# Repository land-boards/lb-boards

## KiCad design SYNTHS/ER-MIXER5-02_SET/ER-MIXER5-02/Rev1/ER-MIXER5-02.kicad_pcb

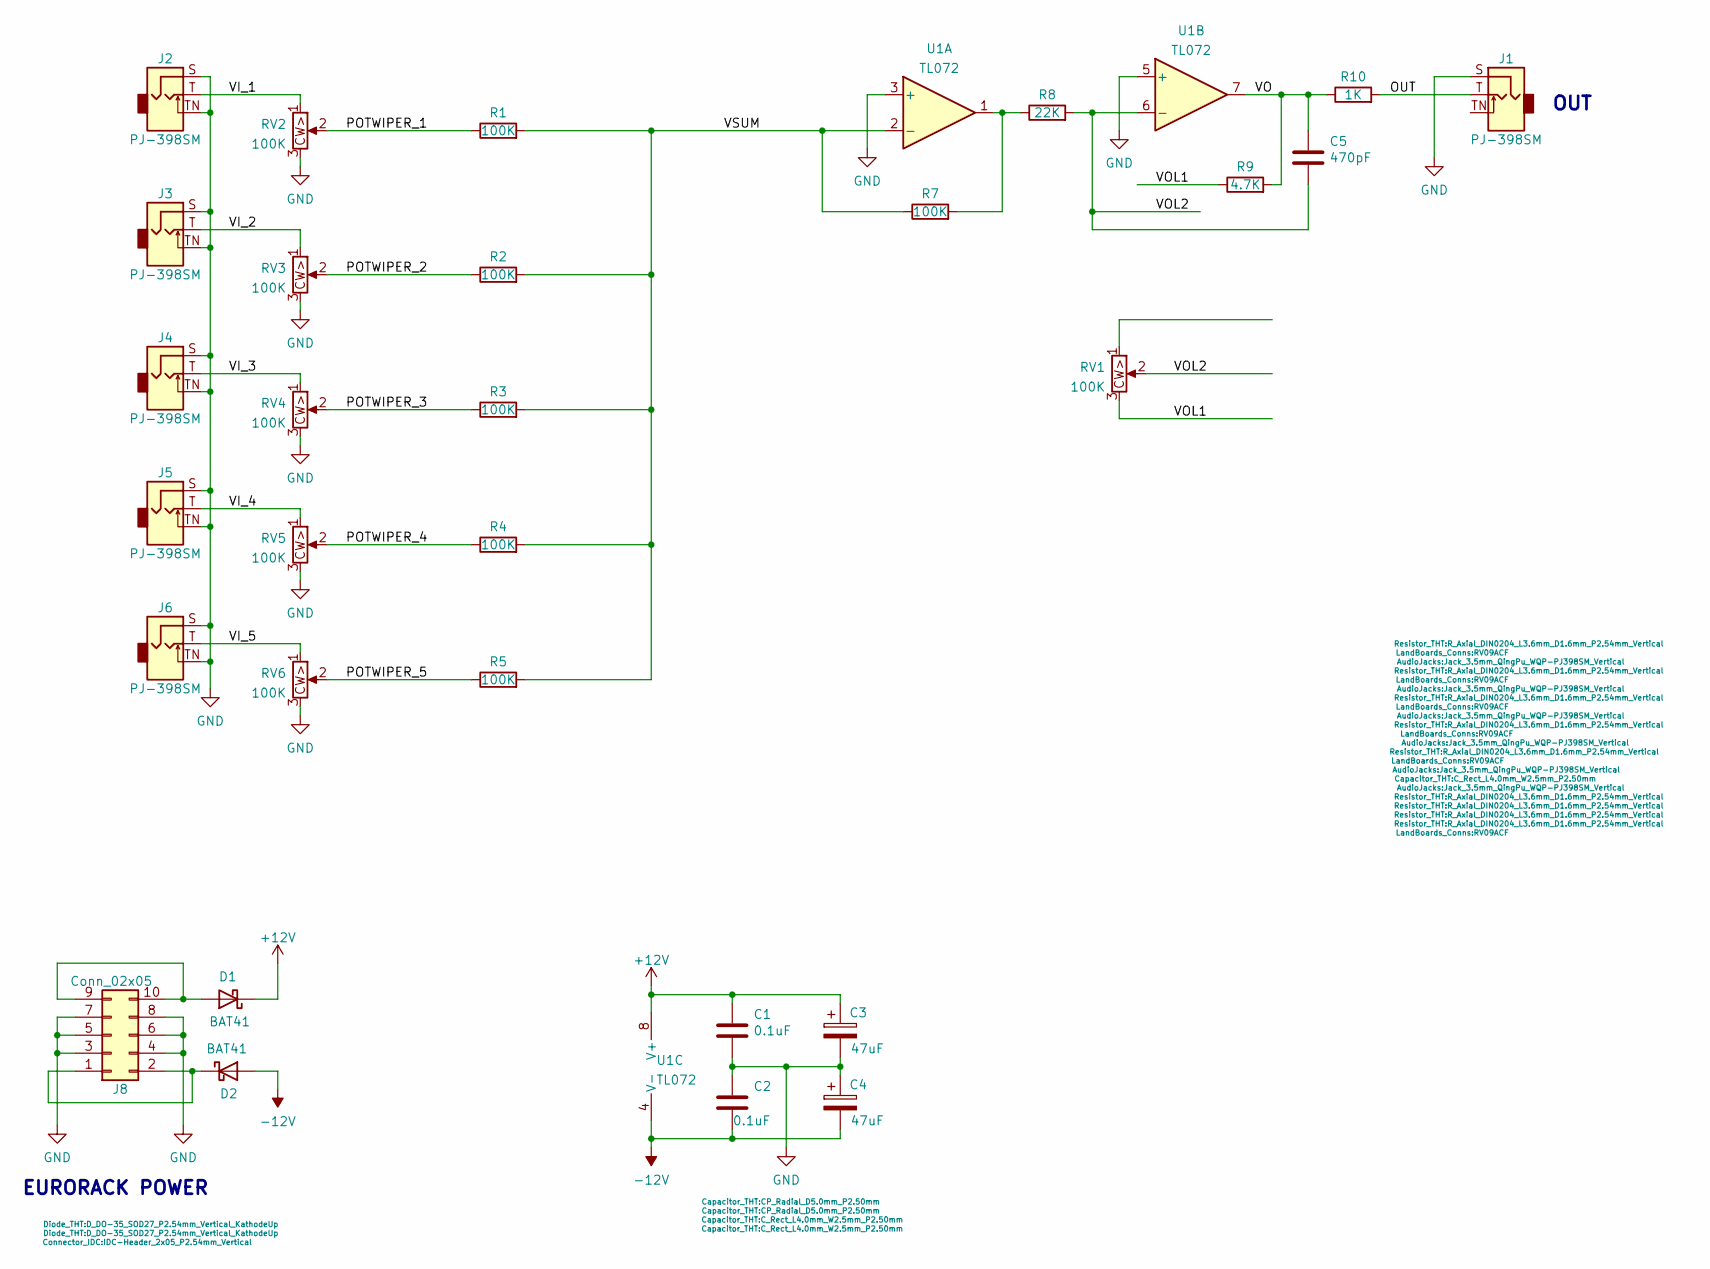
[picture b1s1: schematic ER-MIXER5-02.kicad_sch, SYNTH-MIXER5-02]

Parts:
C1, C2: 0.1uF; C_Rect_L4.0mm_W2.5mm_P2.50mm
C3, C4: 47uF; CP_Radial_D5.0mm_P2.50mm
C5: 470pF; C_Rect_L4.0mm_W2.5mm_P2.50mm
D1, D2: BAT41; D_DO-35_SOD27_P2.54mm_Vertical_KathodeUp
J1, J2, J3, J4, J5, J6: PJ-398SM; Jack_3.5mm_QingPu_WQP-PJ398SM_Vertical
J8: Conn_02x05; IDC-Header_2x05_P2.54mm_Vertical
R1, R2, R3, R4, R5, R7: 100K; R_Axial_DIN0204_L3.6mm_D1.6mm_P2.54mm_Vertical
R8: 22K; R_Axial_DIN0204_L3.6mm_D1.6mm_P2.54mm_Vertical
R9: 4.7K; R_Axial_DIN0204_L3.6mm_D1.6mm_P2.54mm_Vertical
R10: 1K; R_Axial_DIN0204_L3.6mm_D1.6mm_P2.54mm_Vertical
RV1, RV2, RV3, RV4, RV5, RV6: 100K; RV09ACF
U1: TL072; DIP-8_W7.62mm

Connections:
+12V: C1.1, C3.1, D1.1 (K), U1.8 (V+)
-12V: C2.2, C4.2, D2.2 (A), U1.4 (V-)
/OUT: J1.T, R10.2
/POTWIPER_1: R1.1, RV2.2
/POTWIPER_2: R2.1, RV3.2
/POTWIPER_3: R3.1, RV4.2
/POTWIPER_4: R4.1, RV5.2
/POTWIPER_5: R5.1, RV6.2
/VI_1: J2.T, RV2.1
/VI_2: J3.T, RV3.1
/VI_3: J4.T, RV4.1
/VI_4: J5.T, RV5.1
/VI_5: J6.T, RV6.1
/VO: C5.1, R9.2, R10.1, U1.7
/VOL1: R9.1, RV1.3
/VOL2: C5.2, R8.2, RV1.2, U1.6 (-)
/VSUM: R1.2, R2.2, R3.2, R4.2, R5.2, R7.1, U1.2 (-)
GND: C1.2, C2.1, C3.2, C4.1, J1.S, J2.S, J2.TN, J3.S, J3.TN, J4.S, J4.TN, J5.S, J5.TN, J6.S, J6.TN, J8.3, J8.4, J8.5, J8.6, J8.7, J8.8, RV2.3, RV3.3, RV4.3, RV5.3, RV6.3, U1.3 (+), U1.5 (+)
unnamed: D1.2 (A), J8.9, J8.10
unnamed: D2.1 (K), J8.1, J8.2
unnamed: R7.2, R8.1, U1.1

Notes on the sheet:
EURORACK POWER
OUT

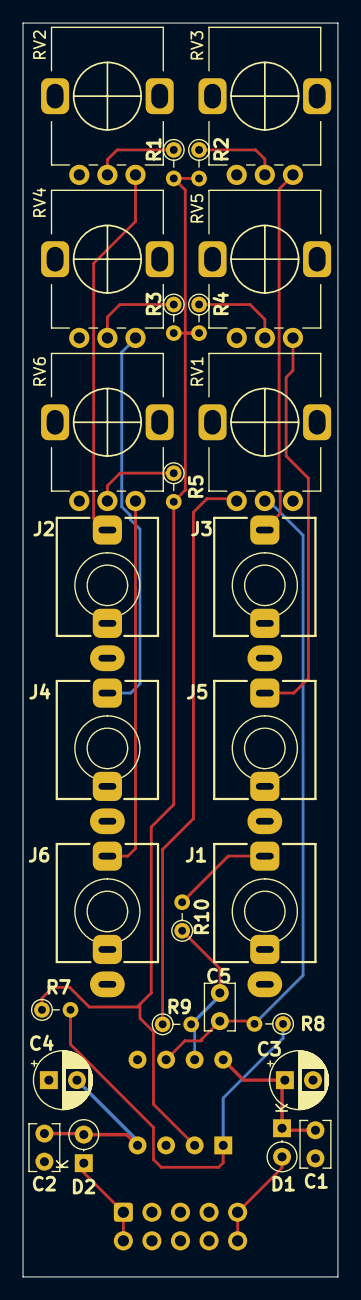
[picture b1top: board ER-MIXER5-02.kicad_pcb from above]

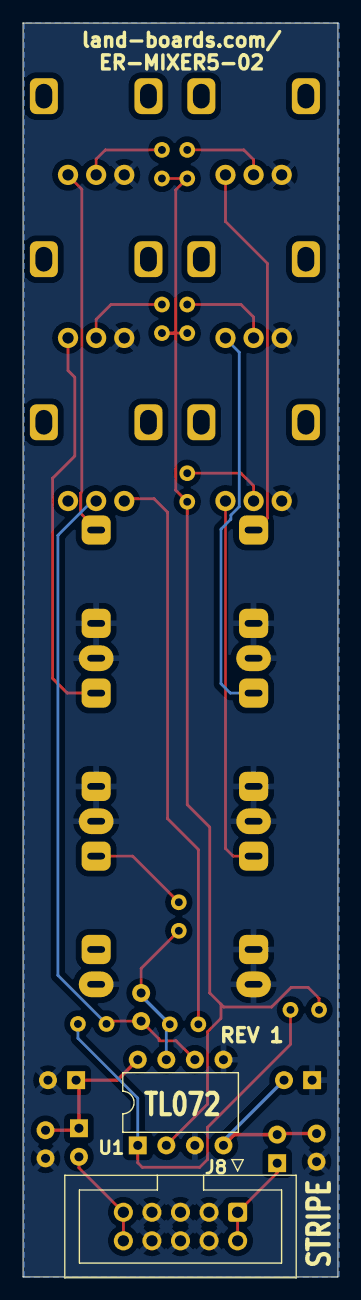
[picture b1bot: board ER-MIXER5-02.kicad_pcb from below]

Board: 2 copper layers, 28.0 x 111.5 mm, 30 parts (2 on the bottom side), 21 nets.

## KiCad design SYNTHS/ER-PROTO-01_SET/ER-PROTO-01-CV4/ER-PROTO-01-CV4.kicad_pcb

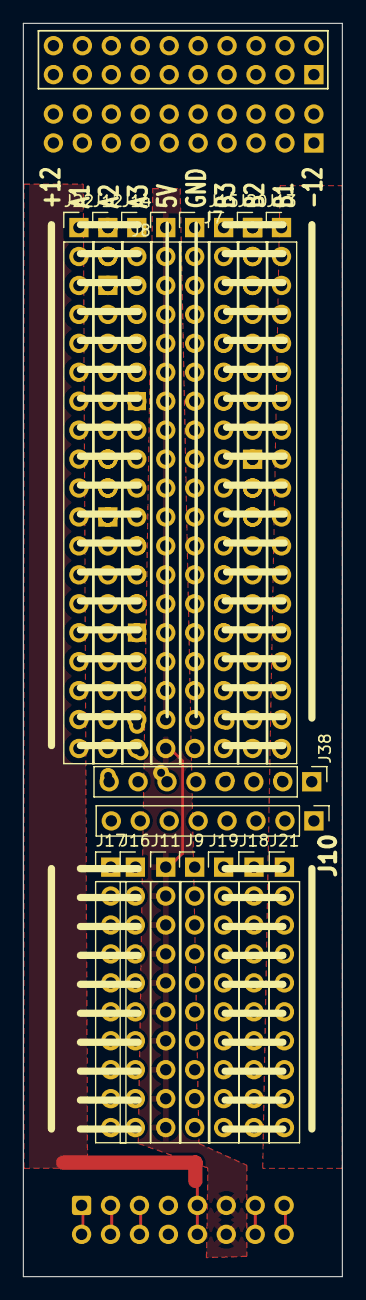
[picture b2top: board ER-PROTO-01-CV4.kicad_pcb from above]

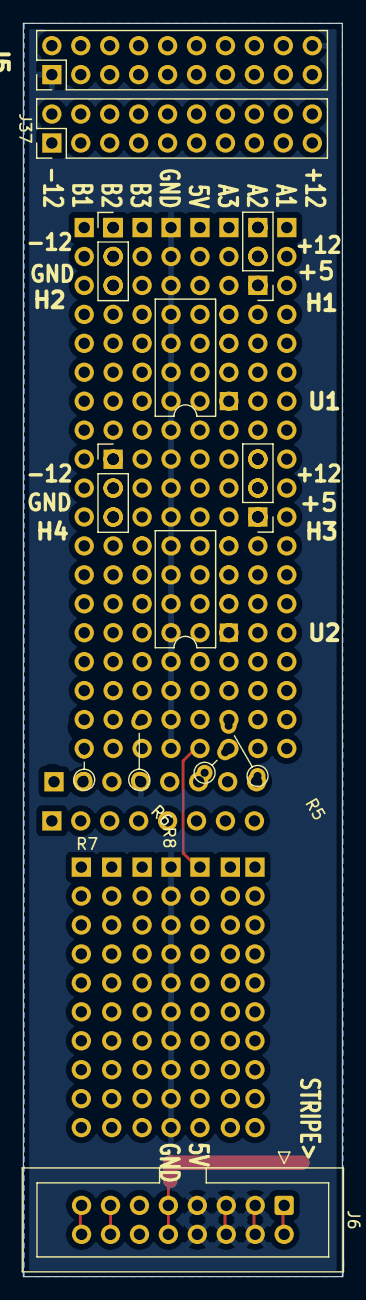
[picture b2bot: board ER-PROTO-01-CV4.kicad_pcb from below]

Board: 2 copper layers, 28.0 x 110.0 mm, 30 parts (13 on the bottom side), 27 nets.

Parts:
H1, H2, H3, H4: Conn_01x03; PinHeader_1x03_P2.54mm_Vertical
J5: HEADER, 2X10; PinHeader_2x10_P2.54mm_Vertical
J6: HEADER, 2X8; IDC-Header_2x08_P2.54mm_Vertical
J7, J8, J12, J13, J14, J15, J20, J22: Conn_01x19; PinHeader_1x19_P2.54mm_Vertical
J9, J11, J16, J17, J18, J19, J21: Conn_01x10; PinHeader_1x10_P2.54mm_Vertical
J10: Conn_01x08; PinHeader_1x08_P2.54mm_Vertical
J37: PROTO01_POTS; PinHeader_2x10_P2.54mm_Vertical
J38: PROTO01_JACKS; PinHeader_1x08_P2.54mm_Vertical
R5, R8: 1K; R_Axial_DIN0204_L3.6mm_D1.6mm_P5.08mm_Vertical
R6, R7: 1K; R_Axial_DIN0204_L3.6mm_D1.6mm_P2.54mm_Vertical
U1, U2: TL072; DIP-8_W7.62mm

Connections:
+5V: H1.1, H3.1, J6.11, J6.12, J8.1, J8.2, J8.3, J8.4, J8.5, J8.6, J8.7, J8.8, J8.9, J8.10, J8.11, J8.12, J8.13, J8.14, J8.15, J8.16, J8.17, J8.18, J8.19, J11.1, J11.2, J11.3, J11.4, J11.5, J11.6, J11.7, J11.8, J11.9, J11.10
+12V: H1.3, H3.3, J6.9, J6.10
-12V: H2.1, H4.1, J6.1, J6.2
/CV: J6.13, J6.14
/GATE: J6.15, J6.16
/J1-T: J38.8 (J1_T), R5.1
/J2-T: J38.4 (J2_T), R8.1
/J3-T: J38.6 (J3_T), R6.1
/J4-S_X: J10.1, J10.3, J10.5, J10.7
/J4-T: J38.2 (J4_T), R7.1
/POT1-1: J5.8, J5.17
/POT1-3: J5.10, J5.19
/POT1W: J37.18 (POT1_2_W), U1.3 (+)
/POT2W: J37.9 (POT2_2_W), U1.5 (+)
/POT3-1: J5.5, J5.14
/POT3-3: J5.7, J5.16
/POT3W: J37.15 (POT3_2_W), U2.3 (+)
/POT4W: J37.6 (POT4_2_W), U2.5 (+)
/VH1: H1.2, J37.8 (POT2_1_CW), U1.8 (V+)
/VH2: H3.2, J37.5 (POT4_1_CW), U2.8 (V+)
/VL1: H2.2, J37.10 (POT2_3_CCW), U1.4 (V-)
/VL2: H4.2, J37.7 (POT4_3_CCW), U2.4 (V-)
GND: H2.3, H4.3, J5.1, J5.20, J6.3, J6.4, J6.5, J6.6, J6.7, J6.8, J7.1, J7.2, J7.3, J7.4, J7.5, J7.6, J7.7, J7.8, J7.9, J7.10, J7.11, J7.12, J7.13, J7.14, J7.15, J7.16, J7.17, J7.18, J7.19, J9.1, J9.2, J9.3, J9.4, J9.5, J9.6, J9.7, J9.8, J9.9, J9.10, J38.5 (J3_S)
unnamed: R5.2, U1.1, U1.2 (-)
unnamed: R8.2, U1.6 (-), U1.7
unnamed: R6.2, U2.1, U2.2 (-)
unnamed: R7.2, U2.6 (-), U2.7

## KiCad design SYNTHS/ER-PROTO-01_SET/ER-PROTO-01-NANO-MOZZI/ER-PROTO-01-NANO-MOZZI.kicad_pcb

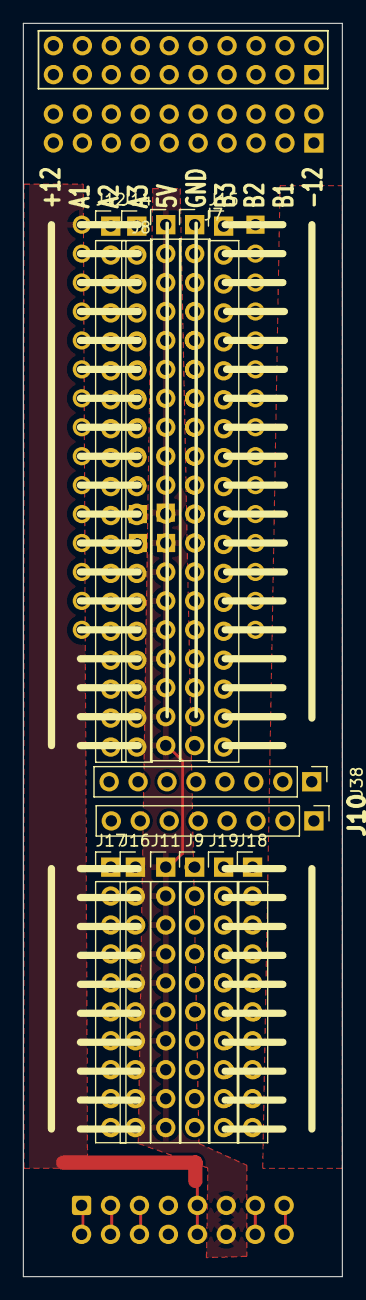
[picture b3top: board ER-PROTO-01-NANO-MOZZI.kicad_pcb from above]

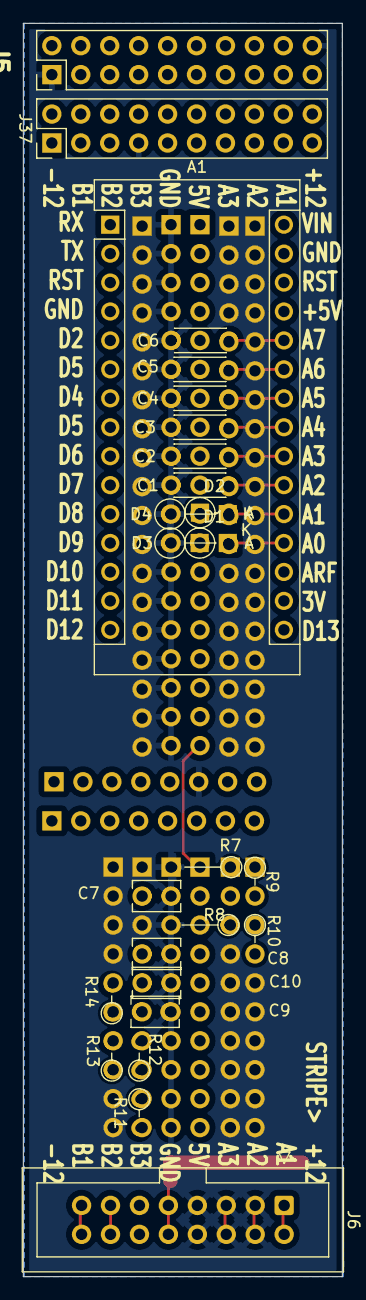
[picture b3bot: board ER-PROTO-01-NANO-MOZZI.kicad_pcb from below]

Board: 2 copper layers, 28.0 x 110.0 mm, 39 parts (26 on the bottom side), 29 nets.

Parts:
A1: Arduino_Nano_v3.x; Arduino_Nano
C1, C2, C3, C4, C5, C6: 0.1uF; C_Disc_D4.3mm_W1.9mm_P5.00mm
C7, C8: 0.1uF; C_Rect_L4.0mm_W2.5mm_P2.50mm
C9: 4.7nF; C_Rect_L4.0mm_W2.5mm_P2.50mm
C10: 10nF; C_Rect_L4.0mm_W2.5mm_P2.50mm
D1, D2: BAT41; D_DO-35_SOD27_P2.54mm_Vertical_AnodeUp
D3, D4: BAT41; D_DO-35_SOD27_P5.08mm_Vertical_KathodeUp
J5: HEADER, 2X10; PinHeader_2x10_P2.54mm_Vertical
J6: HEADER, 2X8; IDC-Header_2x08_P2.54mm_Vertical
J7, J8, J12, J14, J15: Conn_01x19; PinHeader_1x19_P2.54mm_Vertical
J9, J11, J16, J17, J18, J19: Conn_01x10; PinHeader_1x10_P2.54mm_Vertical
J10: Conn_01x08; PinHeader_1x08_P2.54mm_Vertical
J37: PROTO01_POTS; PinHeader_2x10_P2.54mm_Vertical
J38: PROTO01_JACKS; PinHeader_1x08_P2.54mm_Vertical
R7, R8: 100K; R_Axial_DIN0204_L3.6mm_D1.6mm_P5.08mm_Vertical
R9, R10: 10K; R_Axial_DIN0204_L3.6mm_D1.6mm_P2.54mm_Vertical
R11, R14: 3.9K; R_Axial_DIN0204_L3.6mm_D1.6mm_P2.54mm_Vertical
R12, R13: 1M; R_Axial_DIN0204_L3.6mm_D1.6mm_P2.54mm_Vertical

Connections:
+5V: D1.1 (K), D2.1 (K), J6.11, J6.12, J8.1, J8.2, J8.3, J8.4, J8.5, J8.6, J8.7, J8.8, J8.9, J8.10, J8.11, J8.12, J8.13, J8.14, J8.15, J8.16, J8.17, J8.18, J8.19, J11.1, J11.2, J11.3, J11.4, J11.5, J11.6, J11.7, J11.8, J11.9, J11.10
+5VD: A1.27 (+5V), J37.11 (POT5_1_CW)
+12V: A1.30 (VIN), J6.9, J6.10
-12V: J6.1, J6.2
/ANA0: A1.19 (A0), C7.1, D1.2 (A), D3.1 (K), R9.2
/ANA1: A1.20 (A1), C8.1, D2.2 (A), D4.1 (K), R10.2
/ANA2: A1.21 (A2), C1.1, J37.3 (POT6_2_W)
/ANA3: A1.22 (A3), C2.1, J37.6 (POT4_2_W)
/ANA4: A1.23 (A4), C3.1, J37.9 (POT2_2_W)
/ANA5: A1.24 (A5), C4.1, J37.12 (POT5_2_W)
/ANA6: A1.25 (A6), C5.1, J37.15 (POT3_2_W)
/ANA7: A1.26 (A7), C6.1, J37.18 (POT1_2_W)
/CV: J6.13, J6.14
/D9: A1.12 (D9), R11.1
/D10: A1.13 (D10), R12.1, R13.1
/GATE: J6.15, J6.16
/J1-T: J10.8, J38.1 (J1_T), R7.1, R9.1
/J2-S: J10.1, J10.3, J10.5, J10.7
/J2-T: J10.4, J38.5 (J2_T), R8.1, R10.1
/J3-T: J10.6, J38.3 (J3_T)
/J4-T: C10.1, J10.2, J38.7 (J4_T), R14.2
/POT2-1: J5.2, J5.5, J5.8
/POT2-3: J5.4, J5.7, J5.10
/POT5-1: J5.11, J5.14, J5.17
/POT5-3: J5.13, J5.16, J5.19
GND: C1.2, C2.2, C3.2, C4.2, C5.2, C6.2, C7.2, C8.2, C9.2, C10.2, D3.2 (A), D4.2 (A), J5.1, J5.20, J6.3, J6.4, J6.5, J6.6, J6.7, J6.8, J7.1, J7.2, J7.3, J7.4, J7.5, J7.6, J7.7, J7.8, J7.9, J7.10, J7.11, J7.12, J7.13, J7.14, J7.15, J7.16, J7.17, J7.18, J7.19, J9.1, J9.2, J9.3, J9.4, J9.5, J9.6, J9.7, J9.8, J9.9, J9.10, J37.7 (POT4_3_CCW), J38.6 (J2_S), R7.2, R8.2
unnamed: C9.1, R11.2, R12.2, R13.2, R14.1
unnamed: J37.4 (POT6_3_CCW), J37.16 (POT3_3_CCW)
unnamed: J37.8 (POT2_1_CW), J37.14 (POT3_1_CW)

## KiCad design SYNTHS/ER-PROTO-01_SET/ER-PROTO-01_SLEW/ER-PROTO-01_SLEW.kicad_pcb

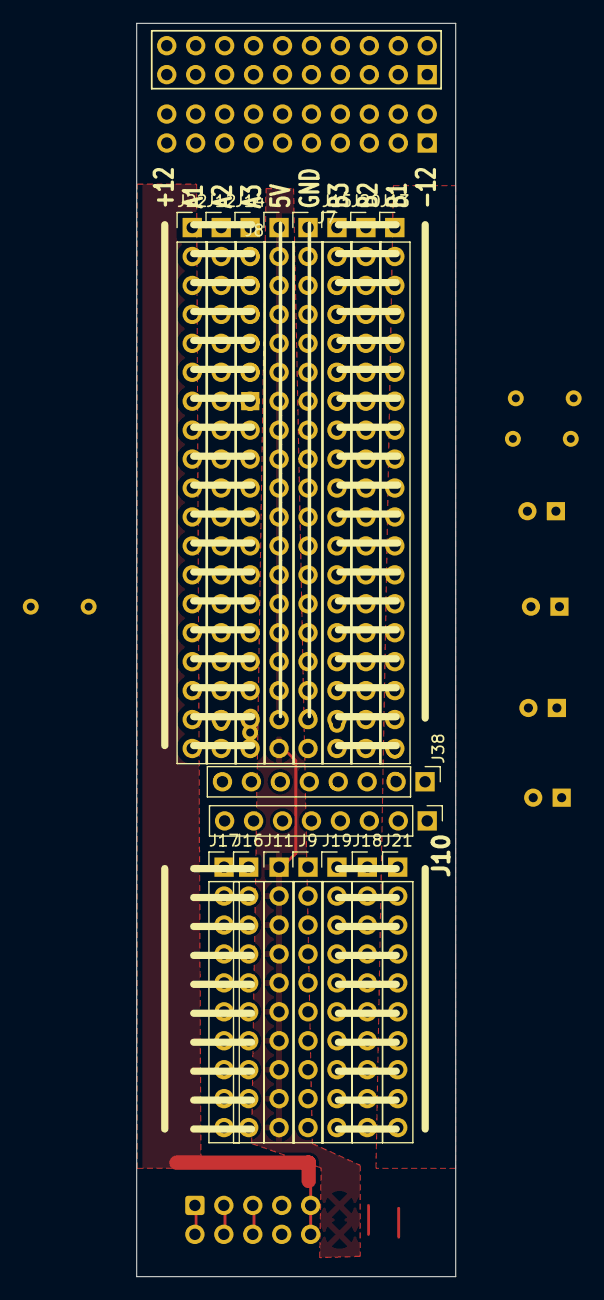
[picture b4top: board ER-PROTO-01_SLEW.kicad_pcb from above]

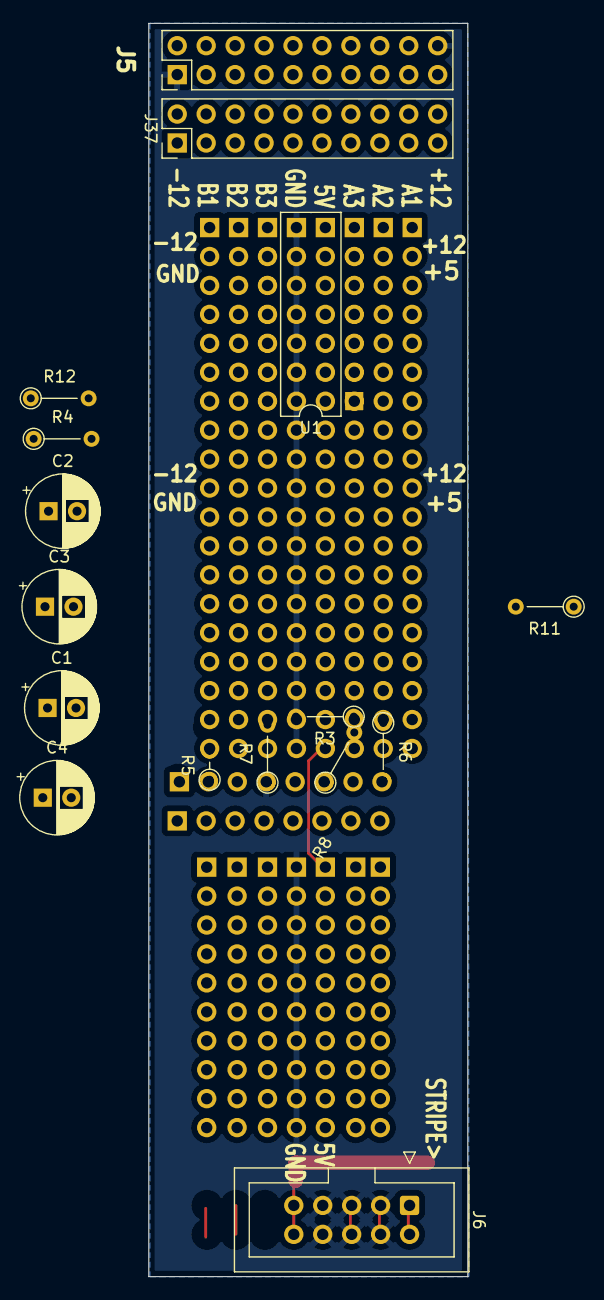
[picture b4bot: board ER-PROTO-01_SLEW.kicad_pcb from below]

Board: 2 copper layers, 28.0 x 110.0 mm, 33 parts (16 on the bottom side), 21 nets.

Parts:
C1, C2, C3, C4: 22uF; CP_Radial_D6.3mm_P2.50mm
J5: HEADER, 2X10; PinHeader_2x10_P2.54mm_Vertical
J6: CONN, IDC, 2X5; IDC-Header_2x05_P2.54mm_Vertical
J7, J8, J12, J13, J14, J15, J20, J22: Conn_01x19; PinHeader_1x19_P2.54mm_Vertical
J9, J11, J16, J17, J18, J19, J21: Conn_01x10; PinHeader_1x10_P2.54mm_Vertical
J10: Conn_01x08; PinHeader_1x08_P2.54mm_Vertical
J37: PROTO01_POTS; PinHeader_2x10_P2.54mm_Vertical
J38: PROTO01_JACKS; PinHeader_1x08_P2.54mm_Vertical
R3, R4, R11, R12: 100K; R_Axial_DIN0204_L3.6mm_D1.6mm_P5.08mm_Vertical
R5: 100; R_Axial_DIN0204_L3.6mm_D1.6mm_P2.54mm_Vertical
R6, R7: 1K; R_Axial_DIN0204_L3.6mm_D1.6mm_P5.08mm_Vertical
R8: 100; R_Axial_DIN0204_L3.6mm_D1.6mm_P5.08mm_Vertical
U1: TL084; DIP-14_W7.62mm

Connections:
+5V: J8.1, J8.2, J8.3, J8.4, J8.5, J8.6, J8.7, J8.8, J8.9, J8.10, J8.11, J8.12, J8.13, J8.14, J8.15, J8.16, J8.17, J8.18, J8.19, J11.1, J11.2, J11.3, J11.4, J11.5, J11.6, J11.7, J11.8, J11.9, J11.10
+12V: J6.9, J6.10, U1.4 (V+)
-12V: J6.1, J6.2, U1.11 (V-)
/J1-S_X: J10.1, J10.3, J10.5, J10.7
/J1-T: J38.8 (J1_T), R3.1, R6.2
/J2-T: J38.4 (J2_T), R4.1, R7.2
/J3-T: J38.6 (J3_T), R8.1
/J4-T: J38.2 (J4_T), R5.1
/POT1-1: J37.17 (POT1_1_CW), U1.1, U1.2 (-)
/POT1-1_X: J5.17, J5.18
/POT1-3: C1.1, J37.19 (POT1_3_CCW), U1.5 (+)
/POT2-1: J37.8 (POT2_1_CW), U1.8, U1.9 (-)
/POT2-1_X: J5.8, J5.9
/POT2-3: C3.1, J37.10 (POT2_3_CCW), U1.12 (+)
GND: C2.1, C4.1, J5.1, J5.20, J6.3, J6.4, J6.5, J6.6, J6.7, J6.8, J7.1, J7.2, J7.3, J7.4, J7.5, J7.6, J7.7, J7.8, J7.9, J7.10, J7.11, J7.12, J7.13, J7.14, J7.15, J7.16, J7.17, J7.18, J7.19, J9.1, J9.2, J9.3, J9.4, J9.5, J9.6, J9.7, J9.8, J9.9, J9.10, J38.5 (J3_S), R3.2, R4.2, R11.2, R12.2
unnamed: C1.2, C2.2
unnamed: C3.2, C4.2
unnamed: R6.1, U1.3 (+)
unnamed: R7.1, U1.10 (+)
unnamed: R5.2, R11.1, U1.13 (-), U1.14
unnamed: R8.2, R12.1, U1.6 (-), U1.7

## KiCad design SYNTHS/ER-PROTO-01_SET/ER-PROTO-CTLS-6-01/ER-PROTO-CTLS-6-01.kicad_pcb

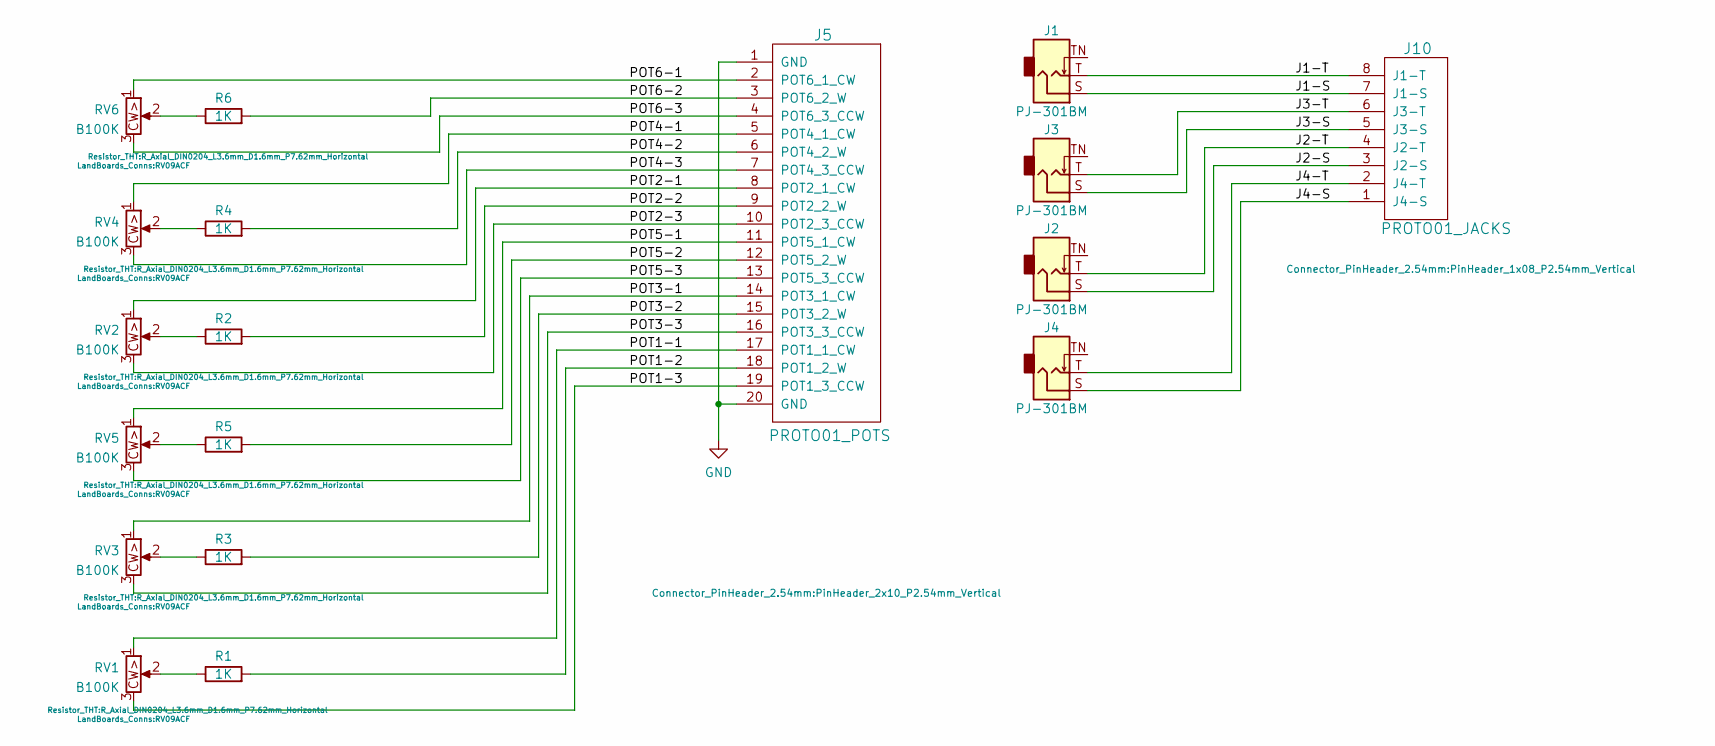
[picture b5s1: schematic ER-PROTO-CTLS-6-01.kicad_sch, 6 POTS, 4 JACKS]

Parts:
J1, J2, J3, J4: PJ-301BM; Jack_3.5mm_QingPu_WQP-PJ301BM_Vertical
J5: PROTO01_POTS; PinHeader_2x10_P2.54mm_Vertical
J10: PROTO01_JACKS; PinHeader_1x08_P2.54mm_Vertical
R1, R2, R3, R4, R5, R6: 1K; R_Axial_DIN0204_L3.6mm_D1.6mm_P7.62mm_Horizontal
RV1, RV2, RV3, RV4, RV5, RV6: B100K; RV09ACF

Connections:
/J1-S: J1.S, J10.7 (J1-S)
/J1-T: J1.T, J10.8 (J1-T)
/J2-S: J2.S, J10.3 (J2-S)
/J2-T: J2.T, J10.4 (J2-T)
/J3-S: J3.S, J10.5 (J3-S)
/J3-T: J3.T, J10.6 (J3-T)
/J4-S: J4.S, J10.1 (J4-S)
/J4-T: J4.T, J10.2 (J4-T)
/POT1-1: J5.17 (POT1_1_CW), RV1.1
/POT1-2: J5.18 (POT1_2_W), R1.2
/POT1-3: J5.19 (POT1_3_CCW), RV1.3
/POT2-1: J5.8 (POT2_1_CW), RV2.1
/POT2-2: J5.9 (POT2_2_W), R2.2
/POT2-3: J5.10 (POT2_3_CCW), RV2.3
/POT3-1: J5.14 (POT3_1_CW), RV3.1
/POT3-2: J5.15 (POT3_2_W), R3.2
/POT3-3: J5.16 (POT3_3_CCW), RV3.3
/POT4-1: J5.5 (POT4_1_CW), RV4.1
/POT4-2: J5.6 (POT4_2_W), R4.2
/POT4-3: J5.7 (POT4_3_CCW), RV4.3
/POT5-1: J5.11 (POT5_1_CW), RV5.1
/POT5-2: J5.12 (POT5_2_W), R5.2
/POT5-3: J5.13 (POT5_3_CCW), RV5.3
/POT6-1: J5.2 (POT6_1_CW), RV6.1
/POT6-2: J5.3 (POT6_2_W), R6.2
/POT6-3: J5.4 (POT6_3_CCW), RV6.3
GND: J5.1 (GND), J5.20 (GND)
unnamed: R1.1, RV1.2
unnamed: R2.1, RV2.2
unnamed: R3.1, RV3.2
unnamed: R4.1, RV4.2
unnamed: R5.1, RV5.2
unnamed: R6.1, RV6.2

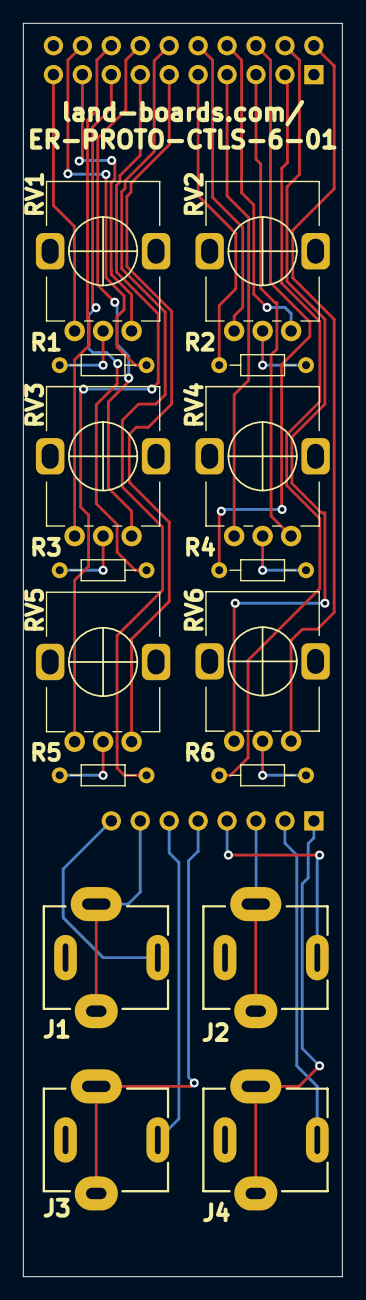
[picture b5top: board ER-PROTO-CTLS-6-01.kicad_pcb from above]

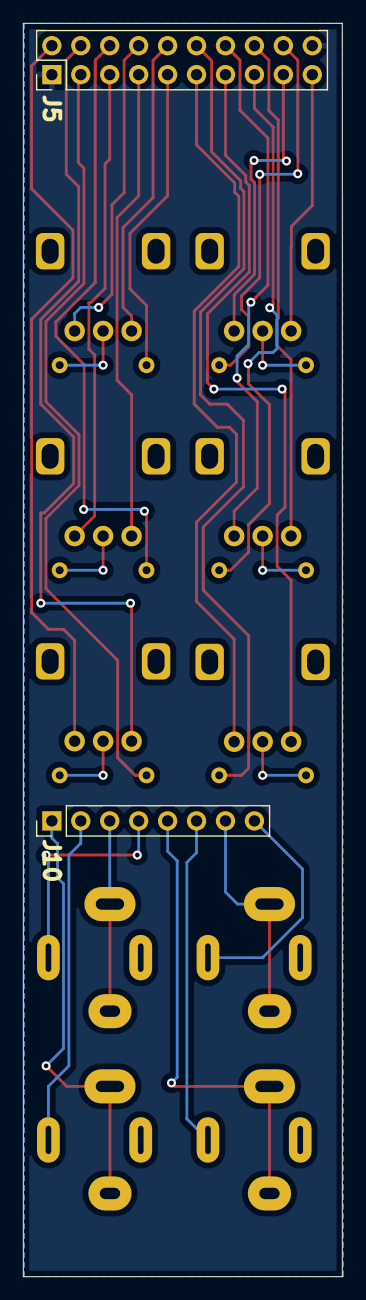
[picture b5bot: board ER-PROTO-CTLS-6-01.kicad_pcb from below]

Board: 2 copper layers, 28.0 x 110.0 mm, 18 parts (2 on the bottom side), 33 nets.

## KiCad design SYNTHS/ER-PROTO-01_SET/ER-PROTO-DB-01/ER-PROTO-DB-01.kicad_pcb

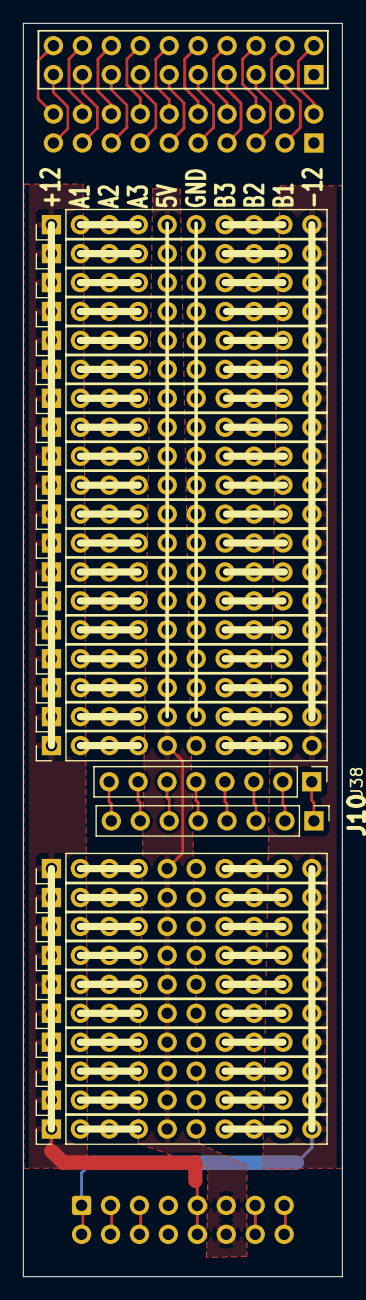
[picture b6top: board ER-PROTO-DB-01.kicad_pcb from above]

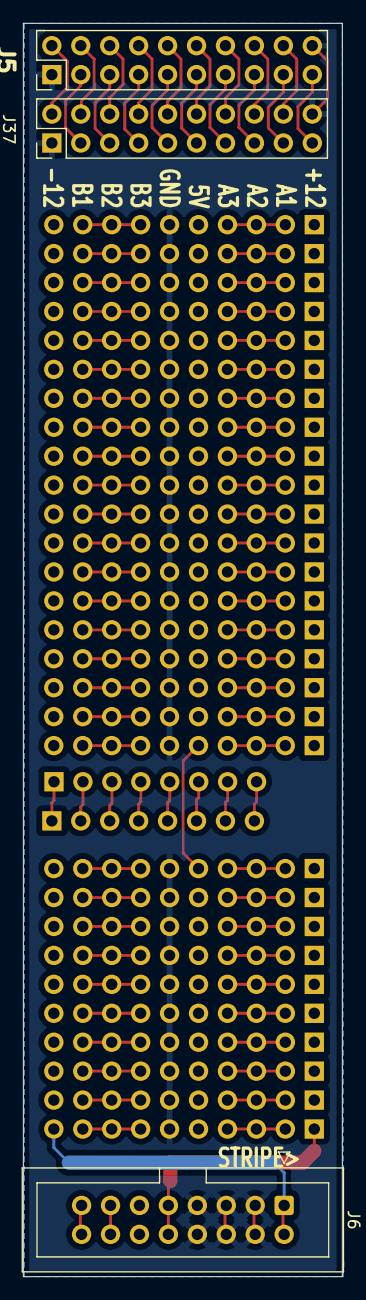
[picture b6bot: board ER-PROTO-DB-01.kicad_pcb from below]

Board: 2 copper layers, 28.0 x 110.0 mm, 34 parts (3 on the bottom side), 90 nets.

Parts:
J5, J37: PROTO01_POTS; PinHeader_2x10_P2.54mm_Vertical
J6: ER-PWR-2X8; IDC-Header_2x08_P2.54mm_Vertical
J7, J8, J9, J11, J12, J13, J14, J15, J16, J17, J18, J19, J20, J21, J22, J23, J24, J25, J26, J27, J28, J29, J30, J31, J32, J33, J34, J35, J36: Conn_01x10; PinHeader_1x10_P2.54mm_Vertical
J10, J38: PROTO01_JACKS; PinHeader_1x08_P2.54mm_Vertical

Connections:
+5V: J6.11 (+5V), J6.12 (+5V), J7.5, J8.5, J9.5, J11.5, J12.5, J13.5, J14.5, J15.5, J16.5, J17.5, J18.5, J19.5, J20.5, J21.5, J22.5, J23.5, J24.5, J25.5, J26.5, J27.5, J28.5, J29.5, J30.5, J31.5, J32.5, J33.5, J34.5, J35.5, J36.5
+12V: J6.9 (+12V), J6.10 (+12V), J7.1, J8.1, J9.1, J11.1, J12.1, J13.1, J14.1, J15.1, J16.1, J17.1, J18.1, J19.1, J20.1, J21.1, J22.1, J23.1, J24.1, J25.1, J26.1, J27.1, J28.1, J29.1, J30.1, J31.1, J32.1, J33.1, J34.1, J35.1, J36.1
-12V: J6.1 (-12V), J6.2 (-12V), J7.10, J8.10, J9.10, J11.10, J12.10, J13.10, J14.10, J15.10, J16.10, J17.10, J18.10, J19.10, J20.10, J21.10, J22.10, J23.10, J24.10, J25.10, J26.10, J27.10, J28.10, J29.10, J30.10, J31.10, J32.10, J33.10, J34.10, J35.10, J36.10
/CV: J6.13 (CV), J6.14 (CV)
/GATE: J6.15 (GATE), J6.16 (GATE)
/J1-S: J10.7 (J1-S), J38.7 (J1-S)
/J1-T: J10.8 (J1-T), J38.8 (J1-T)
/J2-S: J10.3 (J2-S), J38.3 (J2-S)
/J2-T: J10.4 (J2-T), J38.4 (J2-T)
/J3-S: J10.5 (J3-S), J38.5 (J3-S)
/J3-T: J10.6 (J3-T), J38.6 (J3-T)
/J4-S: J10.1 (J4-S), J38.1 (J4-S)
/J4-T: J10.2 (J4-T), J38.2 (J4-T)
/POT1-1: J5.17 (POT1_1_CW), J37.17 (POT1_1_CW)
/POT1-2: J5.18 (POT1_2_W), J37.18 (POT1_2_W)
/POT1-3: J5.19 (POT1_3_CCW), J37.19 (POT1_3_CCW)
/POT2-1: J5.8 (POT2_1_CW), J37.8 (POT2_1_CW)
/POT2-2: J5.9 (POT2_2_W), J37.9 (POT2_2_W)
/POT2-3: J5.10 (POT2_3_CCW), J37.10 (POT2_3_CCW)
/POT3-1: J5.14 (POT3_1_CW), J37.14 (POT3_1_CW)
/POT3-2: J5.15 (POT3_2_W), J37.15 (POT3_2_W)
/POT3-3: J5.16 (POT3_3_CCW), J37.16 (POT3_3_CCW)
/POT4-1: J5.5 (POT4_1_CW), J37.5 (POT4_1_CW)
/POT4-2: J5.6 (POT4_2_W), J37.6 (POT4_2_W)
/POT4-3: J5.7 (POT4_3_CCW), J37.7 (POT4_3_CCW)
/POT5-1: J5.11 (POT5_1_CW), J37.11 (POT5_1_CW)
/POT5-2: J5.12 (POT5_2_W), J37.12 (POT5_2_W)
/POT5-3: J5.13 (POT5_3_CCW), J37.13 (POT5_3_CCW)
/POT6-1: J5.2 (POT6_1_CW), J37.2 (POT6_1_CW)
/POT6-2: J5.3 (POT6_2_W), J37.3 (POT6_2_W)
/POT6-3: J5.4 (POT6_3_CCW), J37.4 (POT6_3_CCW)
GND: J5.1 (GND), J5.20 (GND), J6.3 (GND), J6.4 (GND), J6.5 (GND), J6.6 (GND), J6.7 (GND), J6.8 (GND), J7.6, J8.6, J9.6, J11.6, J12.6, J13.6, J14.6, J15.6, J16.6, J17.6, J18.6, J19.6, J20.6, J21.6, J22.6, J23.6, J24.6, J25.6, J26.6, J27.6, J28.6, J29.6, J30.6, J31.6, J32.6, J33.6, J34.6, J35.6, J36.6, J37.1 (GND), J37.20 (GND)
unnamed: J7.2, J7.3, J7.4
unnamed: J7.7, J7.8, J7.9
unnamed: J8.2, J8.3, J8.4
unnamed: J8.7, J8.8, J8.9
unnamed: J9.2, J9.3, J9.4
unnamed: J9.7, J9.8, J9.9
unnamed: J11.2, J11.3, J11.4
unnamed: J11.7, J11.8, J11.9
unnamed: J12.2, J12.3, J12.4
unnamed: J12.7, J12.8, J12.9
unnamed: J13.2, J13.3, J13.4
unnamed: J13.7, J13.8, J13.9
unnamed: J14.2, J14.3, J14.4
unnamed: J14.7, J14.8, J14.9
unnamed: J15.2, J15.3, J15.4
unnamed: J15.7, J15.8, J15.9
unnamed: J16.2, J16.3, J16.4
unnamed: J16.7, J16.8, J16.9
unnamed: J17.2, J17.3, J17.4
unnamed: J17.7, J17.8, J17.9
unnamed: J18.2, J18.3, J18.4
unnamed: J18.7, J18.8, J18.9
unnamed: J19.2, J19.3, J19.4
unnamed: J19.7, J19.8, J19.9
unnamed: J20.2, J20.3, J20.4
unnamed: J20.7, J20.8, J20.9
unnamed: J21.2, J21.3, J21.4
unnamed: J21.7, J21.8, J21.9
unnamed: J22.2, J22.3, J22.4
unnamed: J22.7, J22.8, J22.9
unnamed: J23.2, J23.3, J23.4
unnamed: J23.7, J23.8, J23.9
unnamed: J24.2, J24.3, J24.4
unnamed: J24.7, J24.8, J24.9
unnamed: J25.2, J25.3, J25.4
unnamed: J25.7, J25.8, J25.9
unnamed: J26.2, J26.3, J26.4
unnamed: J26.7, J26.8, J26.9
unnamed: J27.2, J27.3, J27.4
unnamed: J27.7, J27.8, J27.9
unnamed: J28.2, J28.3, J28.4
unnamed: J28.7, J28.8, J28.9
unnamed: J29.2, J29.3, J29.4
unnamed: J29.7, J29.8, J29.9
unnamed: J30.2, J30.3, J30.4
unnamed: J30.7, J30.8, J30.9
unnamed: J31.2, J31.3, J31.4
unnamed: J31.7, J31.8, J31.9
unnamed: J32.2, J32.3, J32.4
unnamed: J32.7, J32.8, J32.9
unnamed: J33.2, J33.3, J33.4
unnamed: J33.7, J33.8, J33.9
unnamed: J34.2, J34.3, J34.4
unnamed: J34.7, J34.8, J34.9
unnamed: J35.2, J35.3, J35.4
unnamed: J35.7, J35.8, J35.9
unnamed: J36.2, J36.3, J36.4
unnamed: J36.7, J36.8, J36.9

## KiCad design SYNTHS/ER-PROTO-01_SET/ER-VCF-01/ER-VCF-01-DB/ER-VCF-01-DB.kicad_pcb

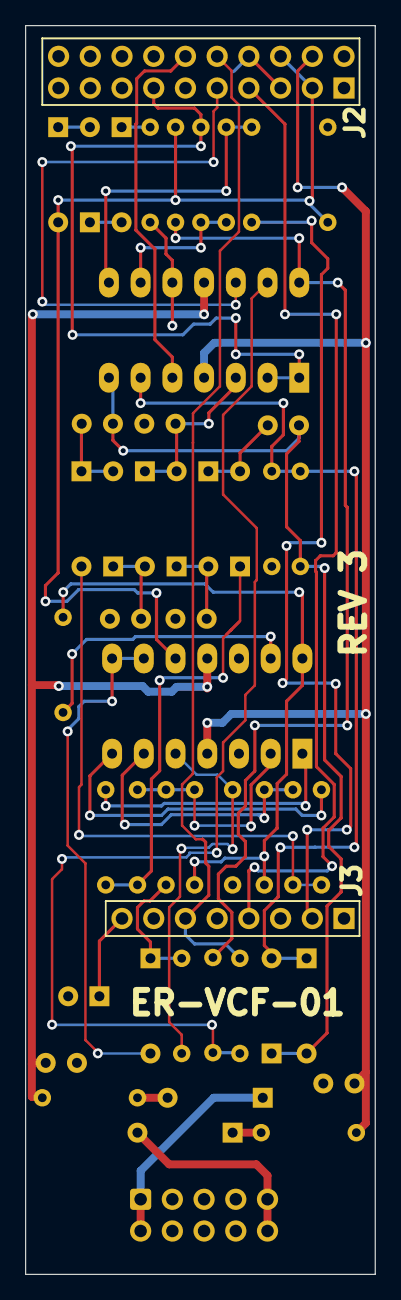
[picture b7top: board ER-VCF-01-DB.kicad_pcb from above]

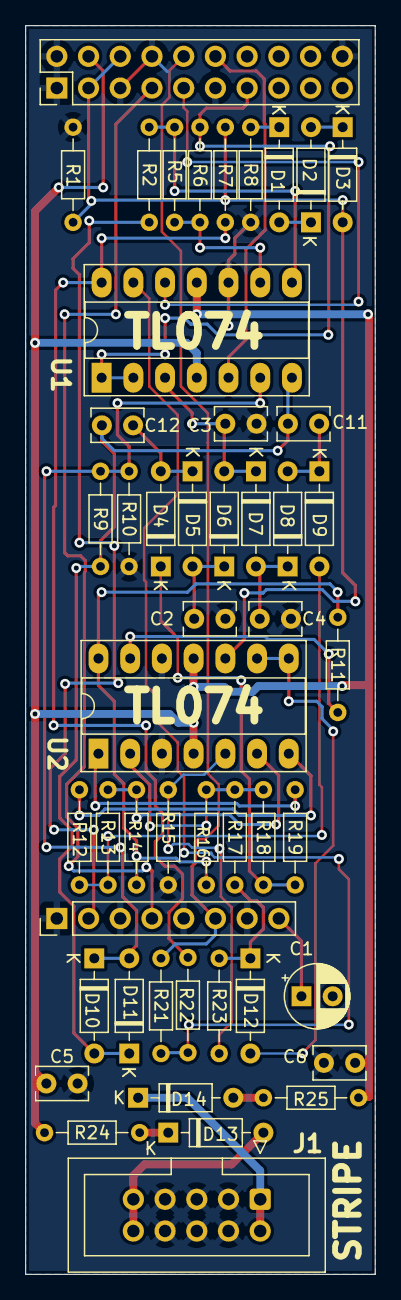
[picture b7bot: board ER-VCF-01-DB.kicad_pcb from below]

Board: 2 copper layers, 28.0 x 100.0 mm, 49 parts (49 on the bottom side), 40 nets.

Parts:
C1: 1uF; CP_Radial_D5.0mm_P2.50mm
C2, C3, C4, C11, C12: 1nF; C_Rect_L4.0mm_W2.5mm_P2.50mm
C5, C6: 0.1uF; C_Rect_L4.0mm_W2.5mm_P2.50mm
D1, D2, D3, D4, D5, D6, D7, D8, D9, D10, D11, D12: 1N4148; D_DO-35_SOD27_P7.62mm_Horizontal
D13, D14: 1N5817; D_DO-35_SOD27_P7.62mm_Horizontal
J1: ER-PWR-2X5; IDC-Header_2x05_P2.54mm_Vertical
J2: PROTO01_POTS; PinHeader_2x10_P2.54mm_Vertical
J3: PROTO01_JACKS; PinHeader_1x08_P2.54mm_Vertical
R1, R9: 10K; R_Axial_DIN0204_L3.6mm_D1.6mm_P7.62mm_Horizontal
R2, R6, R8, R11: 1K; R_Axial_DIN0204_L3.6mm_D1.6mm_P7.62mm_Horizontal
R5: 47K; R_Axial_DIN0204_L3.6mm_D1.6mm_P7.62mm_Horizontal
R7, R21, R22: 100K; R_Axial_DIN0204_L3.6mm_D1.6mm_P7.62mm_Horizontal
R10: 2.7K; R_Axial_DIN0204_L3.6mm_D1.6mm_P7.62mm_Horizontal
R12, R19: 2.2K; R_Axial_DIN0204_L3.6mm_D1.6mm_P7.62mm_Horizontal
R13, R14, R15, R16, R17, R18, R23: 33K; R_Axial_DIN0204_L3.6mm_D1.6mm_P7.62mm_Horizontal
R24, R25: 10; R_Axial_DIN0204_L3.6mm_D1.6mm_P7.62mm_Horizontal
U1, U2: TL074; DIP-14_W7.62mm_Socket_LongPads

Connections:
+12V: C5.1, J2.4 (POT6_3_CCW), R24.2, U1.4 (V+), U2.4 (V+)
-12V: C6.2, R25.2, U1.11 (V-), U2.11 (V-)
/AUDIO: R11.2, R14.1, R16.1, U2.14
/CV: D12.1 (K), R17.1, R23.1
/J1-T: C1.1, J3.8 (J1-T)
/J2-T: J2.7 (POT4_3_CCW), J3.4 (J2-T)
/J3-T: J2.10 (POT2_3_CCW), J3.6 (J3-T), R21.1
/J4-T: J3.2 (J4-T), R2.1
/POT2-2: J2.9 (POT2_2_W), U1.12 (+)
/POT4-2: D3.2 (A), J2.3 (POT6_2_W), J2.6 (POT4_2_W), R1.2, R7.2, U2.10 (+)
/POT5-2: J2.12 (POT5_2_W), U1.5 (+)
/POT5-3: J2.13 (POT5_3_CCW), R6.2, U1.1, U1.2 (-)
GND: C2.2, C3.2, C4.2, C5.2, C6.1, J1.3 (GND), J1.4 (GND), J1.5 (GND), J1.6 (GND), J1.7 (GND), J1.8 (GND), J2.1 (GND), J2.2 (POT6_1_CW), J2.5 (POT4_1_CW), J2.8 (POT2_1_CW), J2.11 (POT5_1_CW), J2.20 (GND), J3.1 (J4-S), J3.3 (J2-S), J3.5 (J3-S), J3.7 (J1-S), R1.1, R8.1, R10.1, R15.1, U1.10 (+), U2.3 (+), U2.12 (+)
unnamed: C2.1, D7.2 (A), D8.1 (K)
unnamed: C3.1, D6.2 (A), D7.1 (K), U1.3 (+)
unnamed: C4.1, D5.2 (A), D6.1 (K)
unnamed: C11.1, C12.1, D10.2 (A), D11.1 (K), R9.1, U1.7
unnamed: C11.2, D8.2 (A), D9.1 (K)
unnamed: C12.2, D4.2 (A), D5.1 (K)
unnamed: D1.1 (K), R8.2
unnamed: D1.2 (A), D2.1 (K)
unnamed: D2.2 (A), D3.1 (K)
unnamed: D4.1 (K), R18.2, R19.2
unnamed: D10.1 (K), D11.2 (A), R9.2, R10.2, U1.6 (-)
unnamed: D12.2 (A), U2.8, U2.9 (-)
unnamed: D13.1 (K), R24.1
unnamed: D13.2 (A), J1.9 (+12V), J1.10 (+12V)
unnamed: D14.1 (K), J1.1 (-12V), J1.2 (-12V)
unnamed: D14.2 (A), R25.1
unnamed: R2.2, R5.2, U1.8
unnamed: R5.1, R6.1, U1.9 (-)
unnamed: R11.1, U2.13 (-)
unnamed: R12.1, U2.7
unnamed: D9.2 (A), R12.2, R13.2
unnamed: R13.1, R14.2, U2.6 (-)
unnamed: R15.2, R23.2, U2.5 (+)
unnamed: R16.2, R17.2, R18.1, U2.2 (-)
unnamed: R19.1, U2.1
unnamed: R21.2, R22.1, U1.13 (-)
unnamed: R7.1, R22.2, U1.14
